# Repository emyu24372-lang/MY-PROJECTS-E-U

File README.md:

# MY-PROJECTS-E-U
This is where you will find my projects .
This project is a 3.5 mm jack-to-USB Type-C adapter that can be plugged into a phone or any other device with a Type-C port.
I was inspired by some commercially available models and designed it with the intention of using it mainly for IEM  headphones .

Here is the BOM table
Referinta,Cantitate,Valoare,Footprint
C1,C2,C7,C8,C9,C12,6,1uF,C_0603_1608Metric
C3,1,3.3uF,C_0603_1608Metric
C4,1,100nF,C_0603_1608Metric
C5,C6,2,15pF,C_0603_1608Metric
C10,C11,2,100pF,C_0603_1608Metric
C13,C14,2,100uF,CP_Elec_6.3x5.4
C15,1,3.3uF,CP_Elec_4x5.4
C16,1,0.22uF,C_0603_1608Metric
J1,1,Conn_01x05,PinHeader_1x05_P2.54mm_Vertical
J2,1,AudioJack4,Jack_3.5mm_PJ320D_Horizontal
L1,1,1uH,L_0805_2012Metric
R1,1,5.1kΩ,R_0603_1608Metric
R2,R3,2,22Ω,R_0603_1608Metric
R4,1,1MΩ,R_0603_1608Metric
R5,1,1kΩ,R_0603_1608Metric
U1,1,PCM2912A,QFP-32_7x7_Pitch0.8mm
Y1,1,6MHz,Crystal_SMD_3225-4Pin_3.2x2.5mm

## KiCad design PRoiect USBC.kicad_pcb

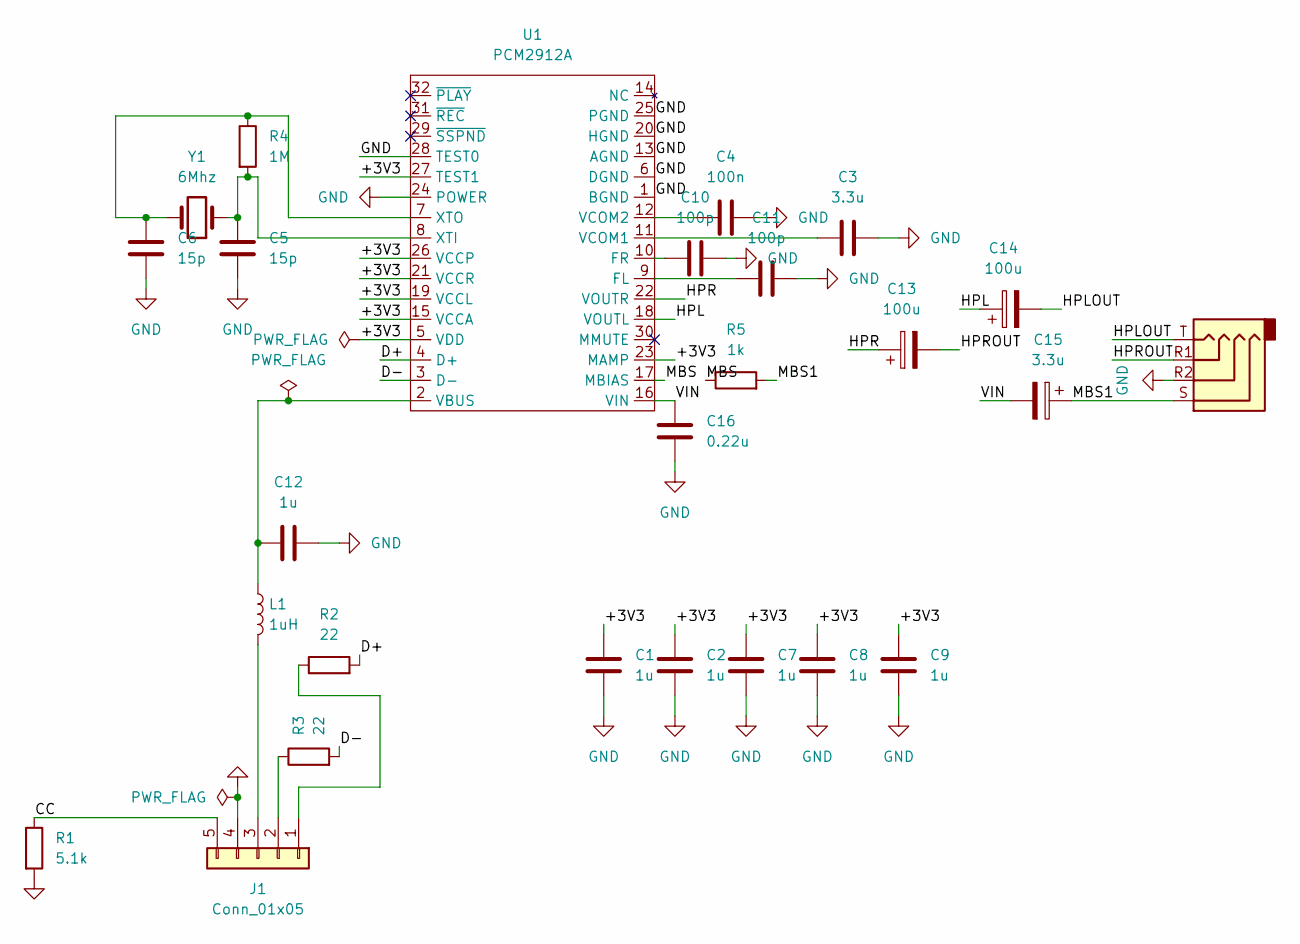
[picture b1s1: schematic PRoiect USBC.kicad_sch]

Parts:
C1, C2, C7, C8, C9, C12: 1u; C_0603_1608Metric
C3: 3.3u; C_0603_1608Metric
C4: 100n; C_0603_1608Metric
C5, C6: 15p; C_0603_1608Metric
C10, C11: 100p; C_0603_1608Metric
C13, C14: 100u; CP_Elec_6.3x5.4
C15: 3.3u; CP_Elec_4x5.4
C16: 0.22u; C_0603_1608Metric
J1: Conn_01x05; PinHeader_1x05_P2.54mm_Vertical
J2: AudioJack4; Jack_3.5mm_PJ320D_Horizontal
L1: 1uH; L_0805_2012Metric
R1: 5.1k; R_0603_1608Metric
R2, R3: 22; R_0603_1608Metric
R4: 1M; R_0603_1608Metric
R5: 1k; R_0603_1608Metric
U1: PCM2912A; QFP-32_7x7_Pitch0.8mm
Y1: 6Mhz; Crystal_SMD_3225-4Pin_3.2x2.5mm

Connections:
/+3V3: C1.1, C2.1, C7.1, C8.1, C9.1, U1.5 (VDD), U1.15 (VCCA), U1.19 (VCCL), U1.21 (VCCR), U1.23 (MAMP), U1.26 (VCCP), U1.27 (TEST1)
/CC: J1.5, R1.1
/D+: R2.2, U1.4 (D+)
/D-: R3.2, U1.3 (D-)
/HPL: C14.1, U1.18 (VOUTL)
/HPLOUT: C14.2, J2.T
/HPR: C13.1, U1.22 (VOUTR)
/HPROUT: C13.2, J2.R1
/MBS: R5.1, U1.17 (MBIAS)
/MBS1: C15.1, J2.S, R5.2
/VIN: C15.2, C16.1, U1.16 (VIN)
GND: C1.2, C2.2, C3.2, C4.2, C5.1, C6.2, C7.2, C8.2, C9.2, C10.2, C11.2, C12.2, C16.2, J1.4, J2.R2, R1.2, U1.1 (BGND), U1.6 (DGND), U1.13 (AGND), U1.20 (HGND), U1.24 (POWER), U1.25 (PGND), U1.28 (TEST0)
unnamed: J1.1, R2.1
unnamed: J1.2, R3.1
unnamed: J1.3, L1.2
unnamed: C11.1, U1.9 (FL)
unnamed: C10.1, U1.10 (FR)
unnamed: C12.1, L1.1, U1.2 (VBUS)
unnamed: C3.1, U1.11 (VCOM1)
unnamed: C4.1, U1.12 (VCOM2)
unnamed: C5.2, R4.2, U1.8 (XTI), Y1.1
unnamed: C6.1, R4.1, U1.7 (XTO), Y1.2

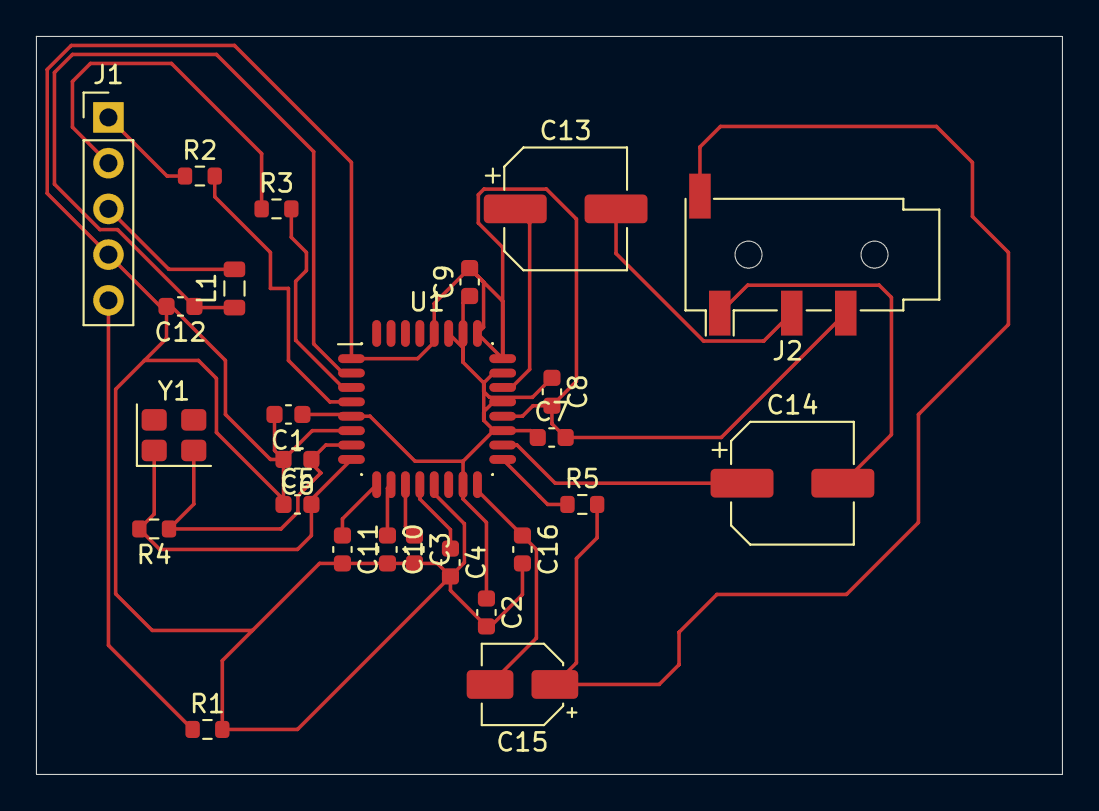
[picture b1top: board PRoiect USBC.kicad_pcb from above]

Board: 2 copper layers, 57.0 x 41.0 mm, 26 parts (0 on the bottom side), 22 nets.

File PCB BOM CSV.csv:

"Reference","Qty","Value","DNP","Exclude from BOM","Exclude from Board","Exclude from Simulation","Exclude from Position Files","Footprint","Datasheet"
"C1,C2,C7,C8,C9,C12","6","1u","","","","","${EXCLUDE_FROM_POS_FILES}","Capacitor_SMD:C_0603_1608Metric",""
"C3","1","3.3u","","","","","${EXCLUDE_FROM_POS_FILES}","Capacitor_SMD:C_0603_1608Metric",""
"C4","1","100n","","","","","${EXCLUDE_FROM_POS_FILES}","Capacitor_SMD:C_0603_1608Metric",""
"C5,C6","2","15p","","","","","${EXCLUDE_FROM_POS_FILES}","Capacitor_SMD:C_0603_1608Metric",""
"C10,C11","2","100p","","","","","${EXCLUDE_FROM_POS_FILES}","Capacitor_SMD:C_0603_1608Metric",""
"C13,C14","2","100u","","","","","${EXCLUDE_FROM_POS_FILES}","Capacitor_SMD:CP_Elec_6.3x5.4",""
"C15","1","3.3u","","","","","${EXCLUDE_FROM_POS_FILES}","Capacitor_SMD:CP_Elec_4x5.4",""
"C16","1","0.22u","","","","","${EXCLUDE_FROM_POS_FILES}","Capacitor_SMD:C_0603_1608Metric",""
"J1","1","Conn_01x05","","","","","${EXCLUDE_FROM_POS_FILES}","Connector_PinHeader_2.54mm:PinHeader_1x05_P2.54mm_Vertical",""
"J2","1","AudioJack4","","","","","${EXCLUDE_FROM_POS_FILES}","Connector_Audio:Jack_3.5mm_PJ320D_Horizontal",""
"L1","1","1uH","","","","","${EXCLUDE_FROM_POS_FILES}","Inductor_SMD:L_0805_2012Metric",""
"R1","1","5.1k","","","","","${EXCLUDE_FROM_POS_FILES}","Resistor_SMD:R_0603_1608Metric",""
"R2,R3","2","22","","","","","${EXCLUDE_FROM_POS_FILES}","Resistor_SMD:R_0603_1608Metric",""
"R4","1","1M","","","","","${EXCLUDE_FROM_POS_FILES}","Resistor_SMD:R_0603_1608Metric",""
"R5","1","1k","","","","","${EXCLUDE_FROM_POS_FILES}","Resistor_SMD:R_0603_1608Metric",""
"U1","1","PCM2912A","","","","","${EXCLUDE_FROM_POS_FILES}","CIP_uSB:QFP-32_7x7_Pitch0.8mm","https://www.ti.com/lit/ds/symlink/pcm2912a.pdf"
"Y1","1","6Mhz","","","","","${EXCLUDE_FROM_POS_FILES}","Crystal:Crystal_SMD_3225-4Pin_3.2x2.5mm",""
